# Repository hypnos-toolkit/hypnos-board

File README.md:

# Hypnos Board 

Hypnos is a hardware and software toolkit which facilitates the creation of energy-aware IoT nodes based on widely extended consumer board platforms: Arduino, LinkIt One and Particle, to mention a few.

The present repository contains the circuit schematics of the Hypnos Board and the source code of the firmware for the ATtiny85 integrated on it.

# Repository contents

The following list describes the different files that can be found in the repository:
* Hypnos Board - Schematic ([EAGLE](./HYPNOS_BOARD_SHIELD_V1.sch), [PDF](./HYPNOS_BOARD_SHIELD_V1.pdf))
* Hypnos Board - Arduino Shield PCB layout ([EAGLE](./HYPNOS_BOARD_SHIELD_V1.brd), [PDF](./HYPNOS_BOARD_SHIELD_V1.brd.pdf))
* ATtiny85 firmware ([INO](./board-microcontroller/microcontroller-firmware.ino))

# Compatibility

The board has been successfully tested on the following microcontroller boards:
* Arduino UNO R3
* SeeedStudio LinkIt One
* Particle Photon (via a Shield-Shield adapter)

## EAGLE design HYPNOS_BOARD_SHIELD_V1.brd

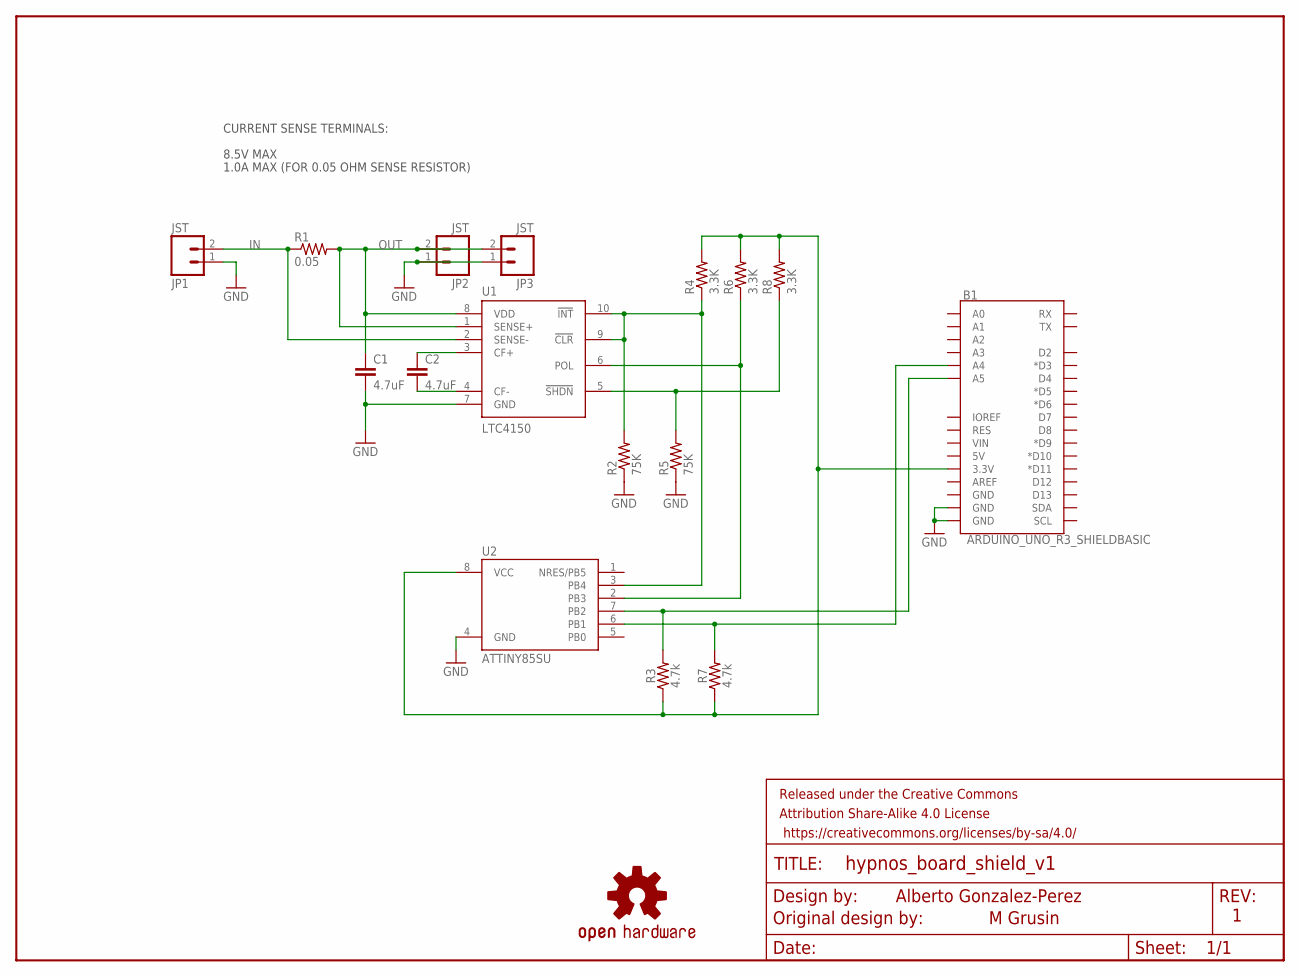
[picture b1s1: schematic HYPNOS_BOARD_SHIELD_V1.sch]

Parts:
B1: ARDUINO_UNO_R3_SHIELDBASIC; UNO_R3_SHIELD
C1, C2: 4.7uF; 0603-CAP
FRAME1: FRAME-LETTER; CREATIVE_COMMONS
JP1, JP2, JP3: JST; JST-2-SMD
LOGO1: OSHW-LOGOS; OSHW-LOGO-S
R1: 0.05; 1206
R2, R5: 75K; 0603-RES
R3, R7: 4.7k; 0603
R4, R6, R8: 3.3K; 0603-RES
U1: LTC4150; MSOP10
U2: ATTINY85SU; ATTINY85

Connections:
3V3: B1.3.3V, R3.1, R4.2, R6.2, R7.1, R8.2, U2.8 (VCC)
!INT!: R2.2, R4.1, U1.9 (!CLR!), U1.10 (!INT!), U2.3 (PB4)
!SHDN!: R5.2, R8.1, U1.5 (!SHDN!)
GND: B1.GND@0 (GND), B1.GND@1 (GND), C1.2, JP1.1 (2), JP2.1 (2), JP3.1 (2), R2.1, R5.1, U1.7 (GND), U2.4 (GND)
IN: JP1.2 (1), R1.1, U1.2 (SENSE-)
unnamed: B1.A5, R3.2, U2.7 (PB2)
unnamed: C2.1, U1.3 (CF+)
unnamed: C2.2, U1.4 (CF-)
OUT: C1.1, JP2.2 (1), JP3.2 (1), R1.2, U1.1 (SENSE+), U1.8 (VDD)
POL: R6.1, U1.6 (POL), U2.2 (PB3)
SDA: B1.A4, R7.2, U2.6 (PB1)

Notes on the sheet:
M Grusin
CURRENT SENSE TERMINALS:
1.0A MAX (FOR 0.05 OHM SENSE RESISTOR)
8.5V MAX
Original design by:
Alberto Gonzalez-Perez

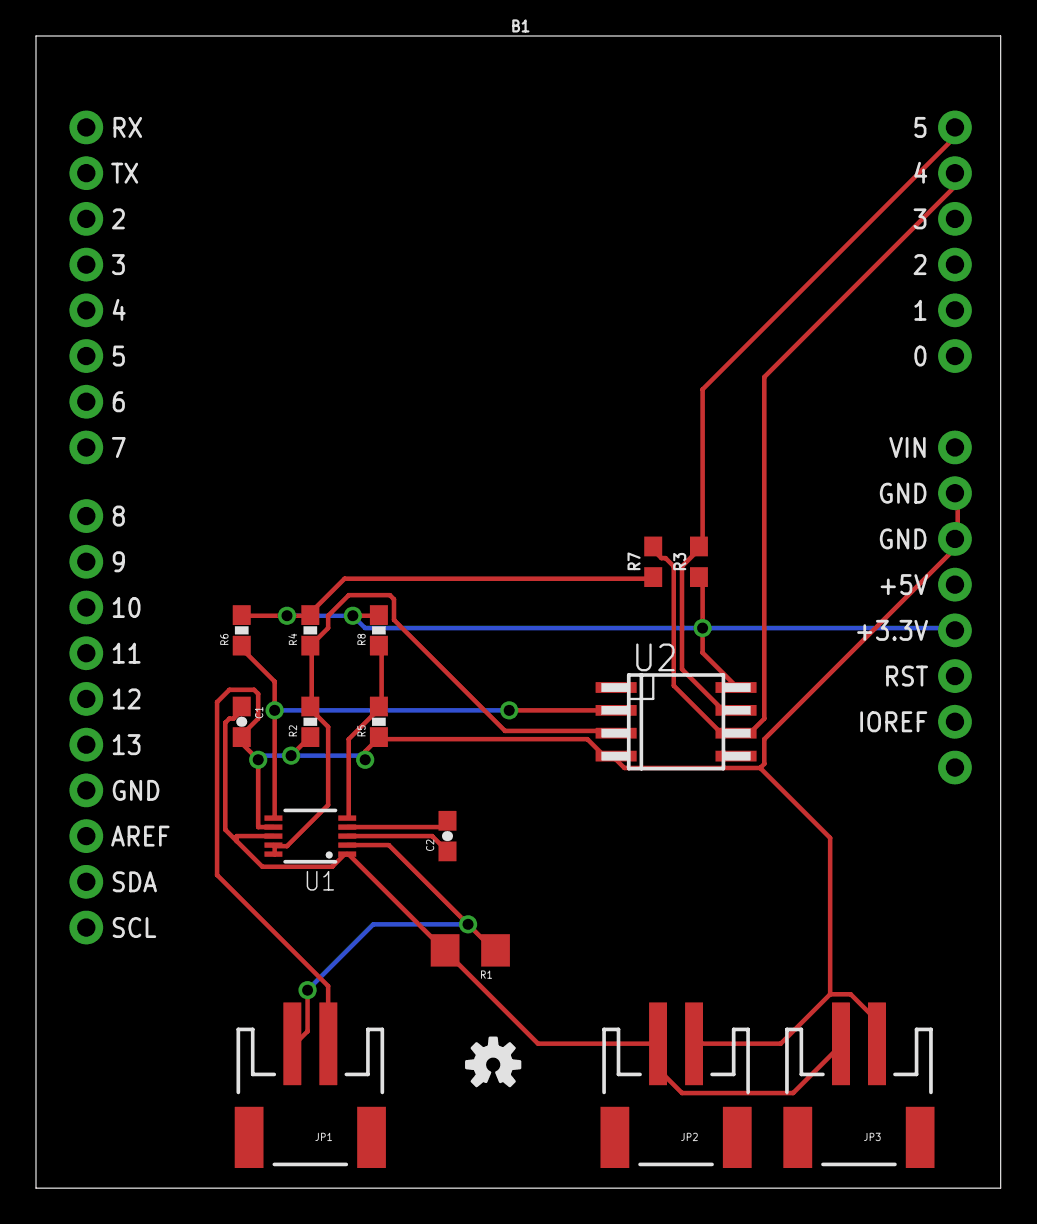
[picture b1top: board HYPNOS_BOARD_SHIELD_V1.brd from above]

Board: 2 copper layers, 53.6 x 64.0 mm, 18 parts (0 on the bottom side), 11 nets.

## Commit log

2016-07-19 Processor fully working
2016-07-19 Rebranding
2016-12-30 Unifying codebase
2017-04-19 Cleaning up comments
2019-08-03 Rename hypnos-board-processor.ino to board-microcontroller/microcontroller-firmware.ino
2019-08-03 Add schematic files
2020-07-30 Create LICENSE

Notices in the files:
parts and their libraries:
SparkFun-Boards: Licensing: Creative Commons ShareAlike 4.0 International - https://creativecommons.org/licenses/by-sa/4.0
SparkFun-Passives: Licensing: CC v3.0 Share-Alike You are welcome to use this library for commercial purposes.
SparkFun-Aesthetics: Released under the Creative Commons
